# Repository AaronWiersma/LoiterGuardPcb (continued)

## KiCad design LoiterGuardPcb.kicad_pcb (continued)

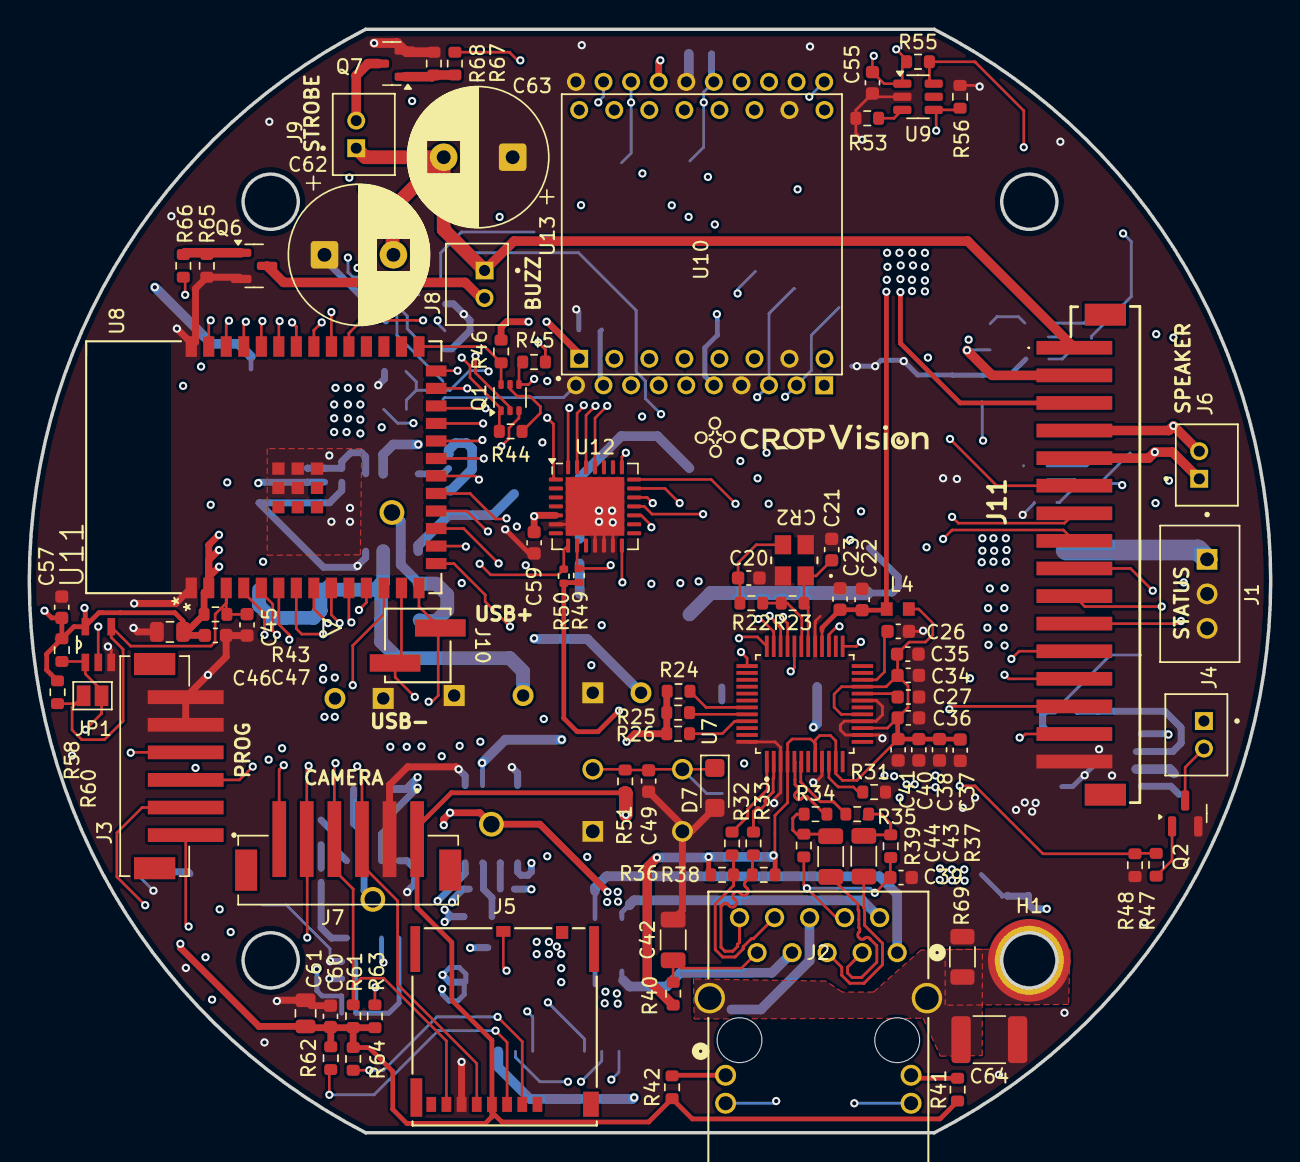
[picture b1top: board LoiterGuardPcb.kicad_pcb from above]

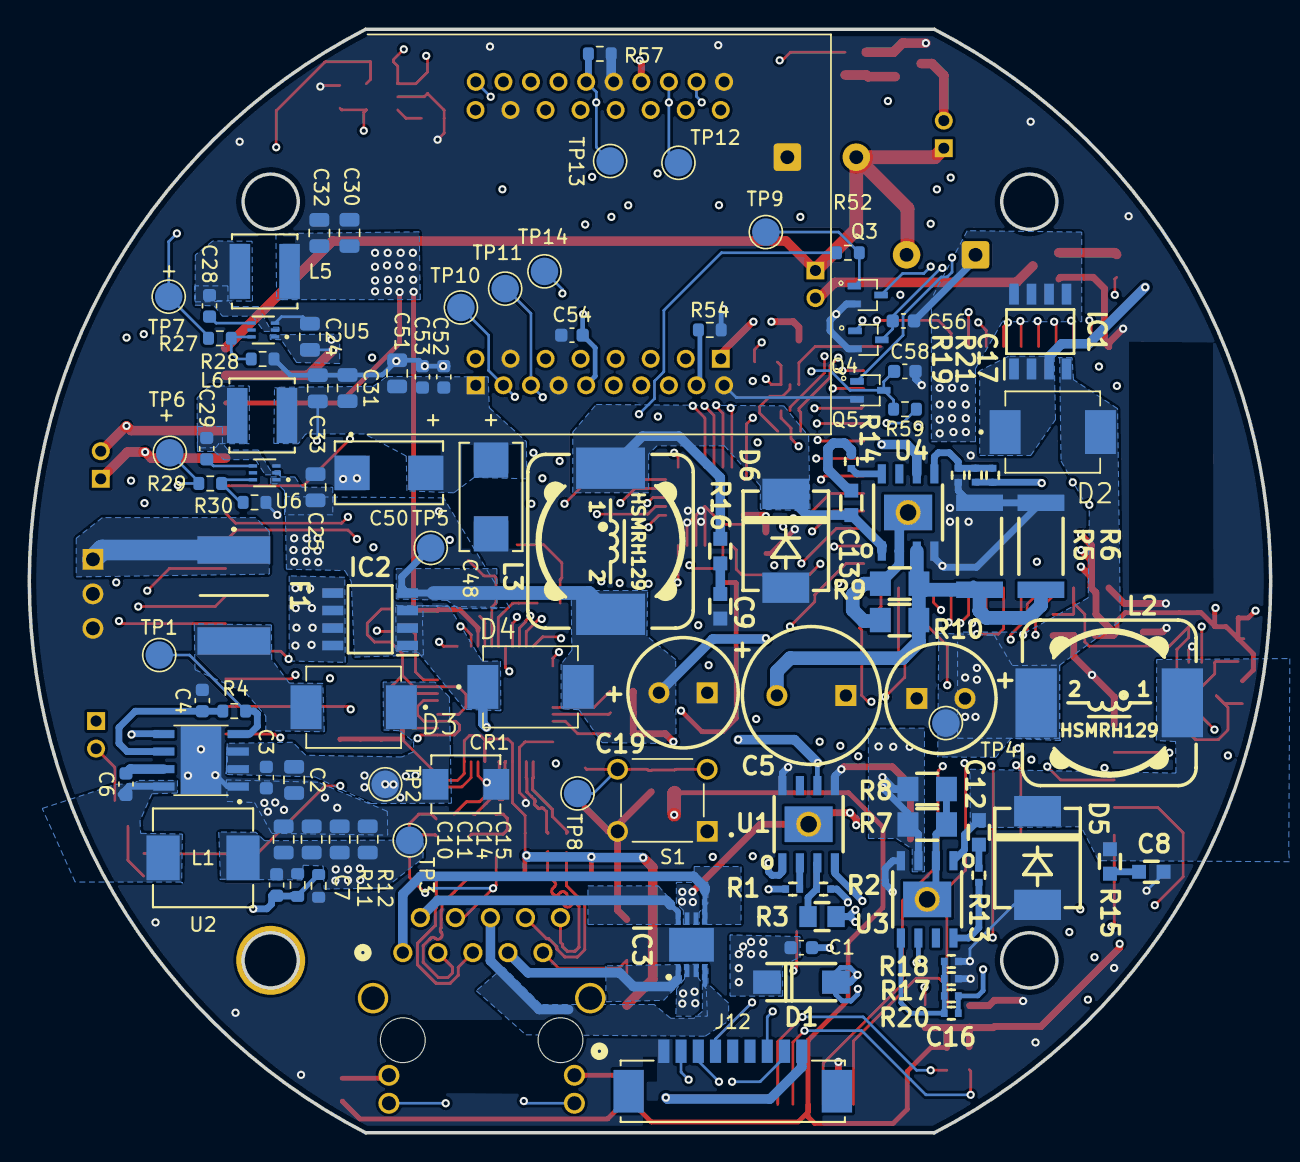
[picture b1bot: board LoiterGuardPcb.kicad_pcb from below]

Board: 6 copper layers, 90.0 x 80.0 mm, 201 parts (106 on the bottom side), 136 nets.

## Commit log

2026-02-07 updated poe schematic
2026-02-08 GPIOs shouldn't have any conflicts
2026-02-08 when using fpc ovo camera
2026-02-09 put all the components on the pcb on traces
2026-02-10 wip - started traces for layout
2026-02-11 wip - still working on layout
2026-02-11 checkpoint
2026-02-11 layout checkin
2026-02-12 WIP - DRC for layout has no errors
2026-02-12 WIP - starting moving reference silkscreens around
2026-02-13 moved 12V connector to the front layer
